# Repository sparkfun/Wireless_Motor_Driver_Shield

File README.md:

SparkFun Wireless Motor Driver Shield
=====================================

[*SparkFun Wireless Motor Driver Shield (DEV-14285)*](https://www.sparkfun.com/products/14285)
Arduino shield with built-in motor driver and XBee slot.

This is an Arduino shield that integrates an H-Bridge Driver and breaks out 
all I/O ports to three-pin headers on a GND / PWR / SIG standard. This enables quick
prototyping and integration of Arduino projects without the need of a breadboard.

This board contains an XBee header for adding wireless capability to your Arduino projects. A switch for 
SW_Serial ties the TX/RX lines to pins A0 and A1 on the Arduino board. 

This shield is a perfect addition to building up a simiple robotics platform with an
Arduino board. Two switches allow you to select which power source is used to power the motors and/or servos.
See [the hookup guide](https://learn.sparkfun.com/tutorials/wireless-motor-driver-shield-hookup-guide#hardware-overview) for a chart showing the various switch configurations.

**Note:** If connected to your Arduino, the switch must be set to SW_Serial in order to program your board. 

Repository Contents
-------------------

* **/Firmware** - Example code 
* **/Hardware** - Eagle design files (.brd, .sch)
* **/Production** - Production panel files (.brd)

Documentation
--------------
* **[Hookup Guide](https://learn.sparkfun.com/tutorials/wireless-motor-driver-shield-hookup-guide)** - Basic hookup guide for the Wireless Motor Driver Shield.
* **[SparkFun Fritzing repo](https://github.com/sparkfun/Fritzing_Parts)** - Fritzing diagrams for SparkFun products.
* **[SparkFun 3D Model repo](https://github.com/sparkfun/3D_Models)** - 3D models of SparkFun products. 

Version History
---------------
* [vH14](https://github.com/sparkfun/Ludus_ProtoShield_Wireless/tree/vH14) - Current version
* [vH11](https://github.com/sparkfun/Ludus_ProtoShield_Wireless/tree/V_1.1) - The product formerly known as the Ludus ProtoShield Wireless

License Information
-------------------

This product is _**open source**_! 

Please review the LICENSE.md file for license information. 

If you have any questions or concerns on licensing, please contact techsupport@sparkfun.com.

Distributed as-is; no warranty is given.

- Your friends at SparkFun.

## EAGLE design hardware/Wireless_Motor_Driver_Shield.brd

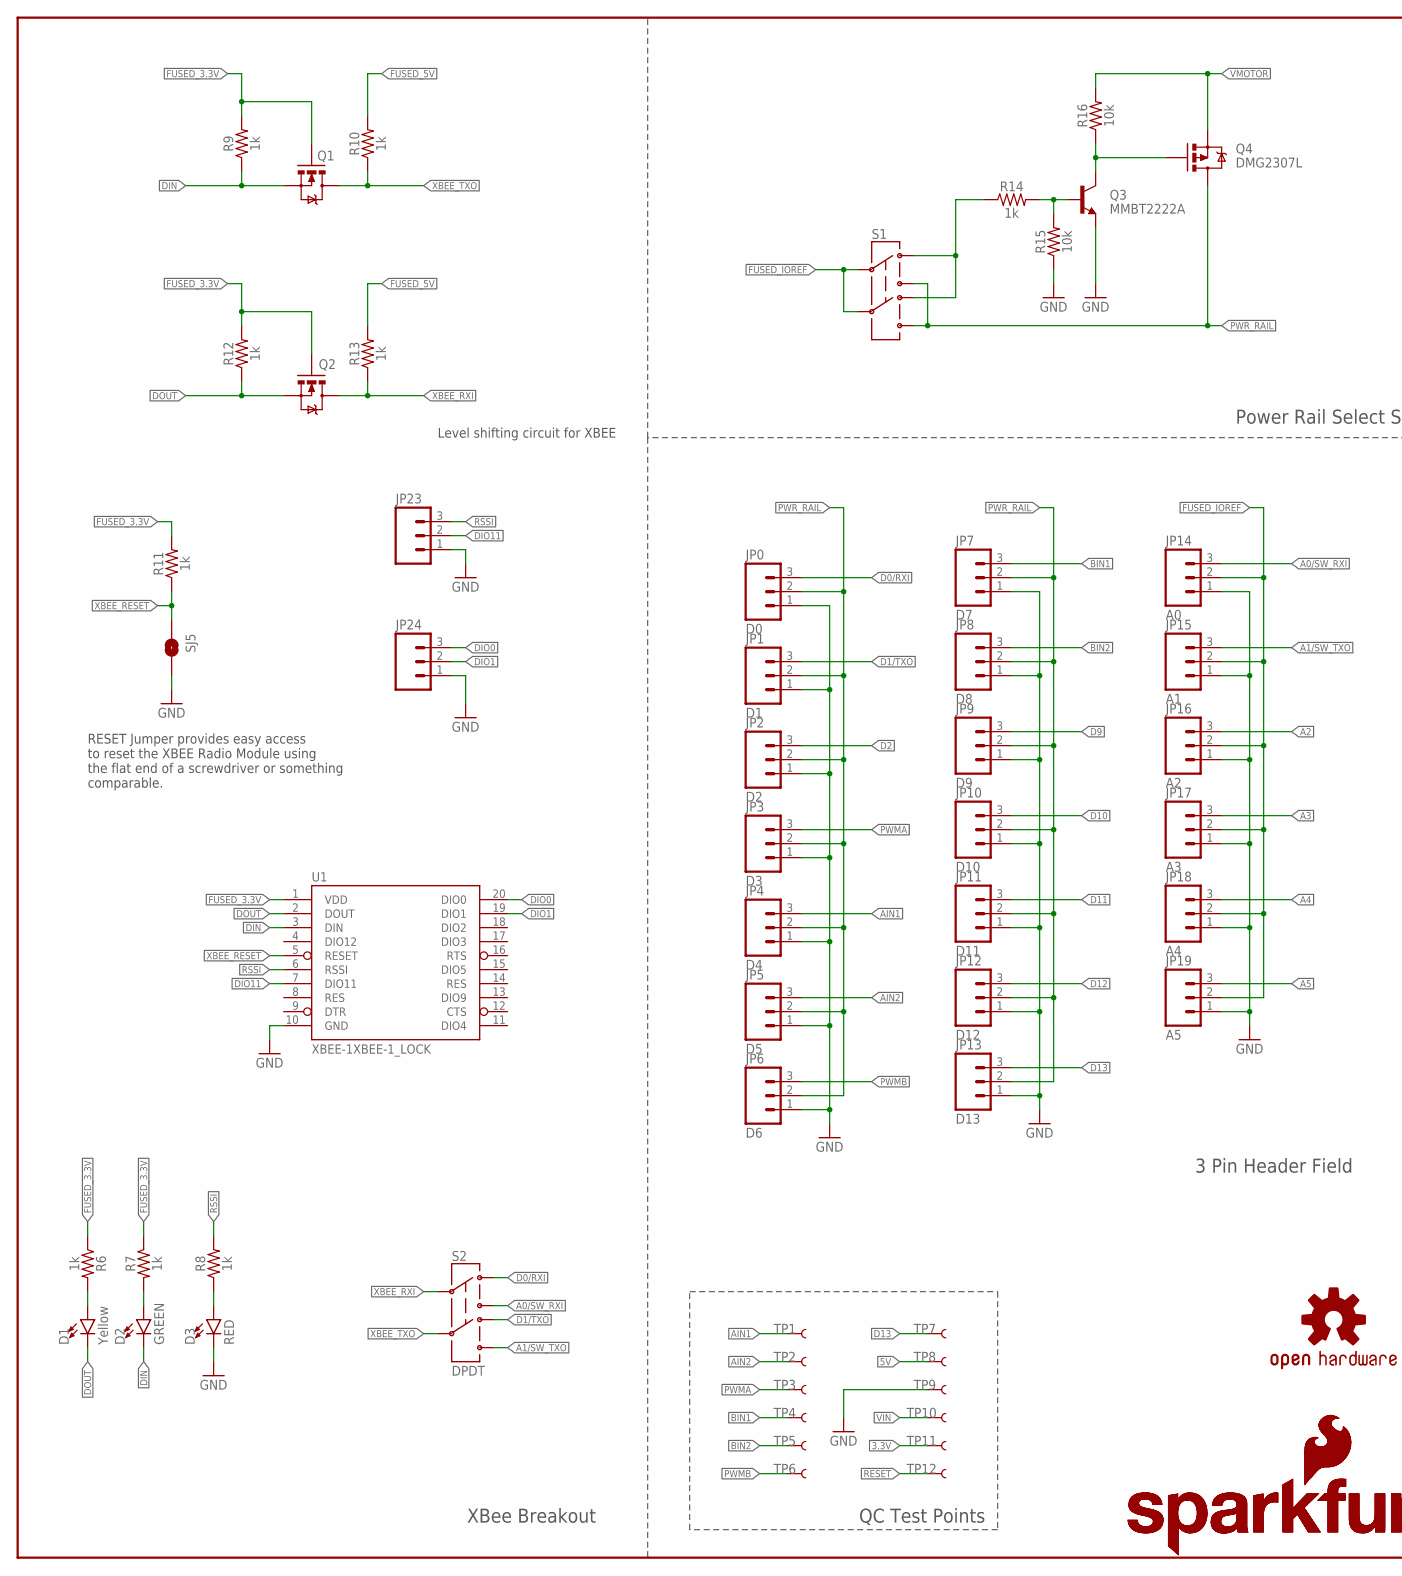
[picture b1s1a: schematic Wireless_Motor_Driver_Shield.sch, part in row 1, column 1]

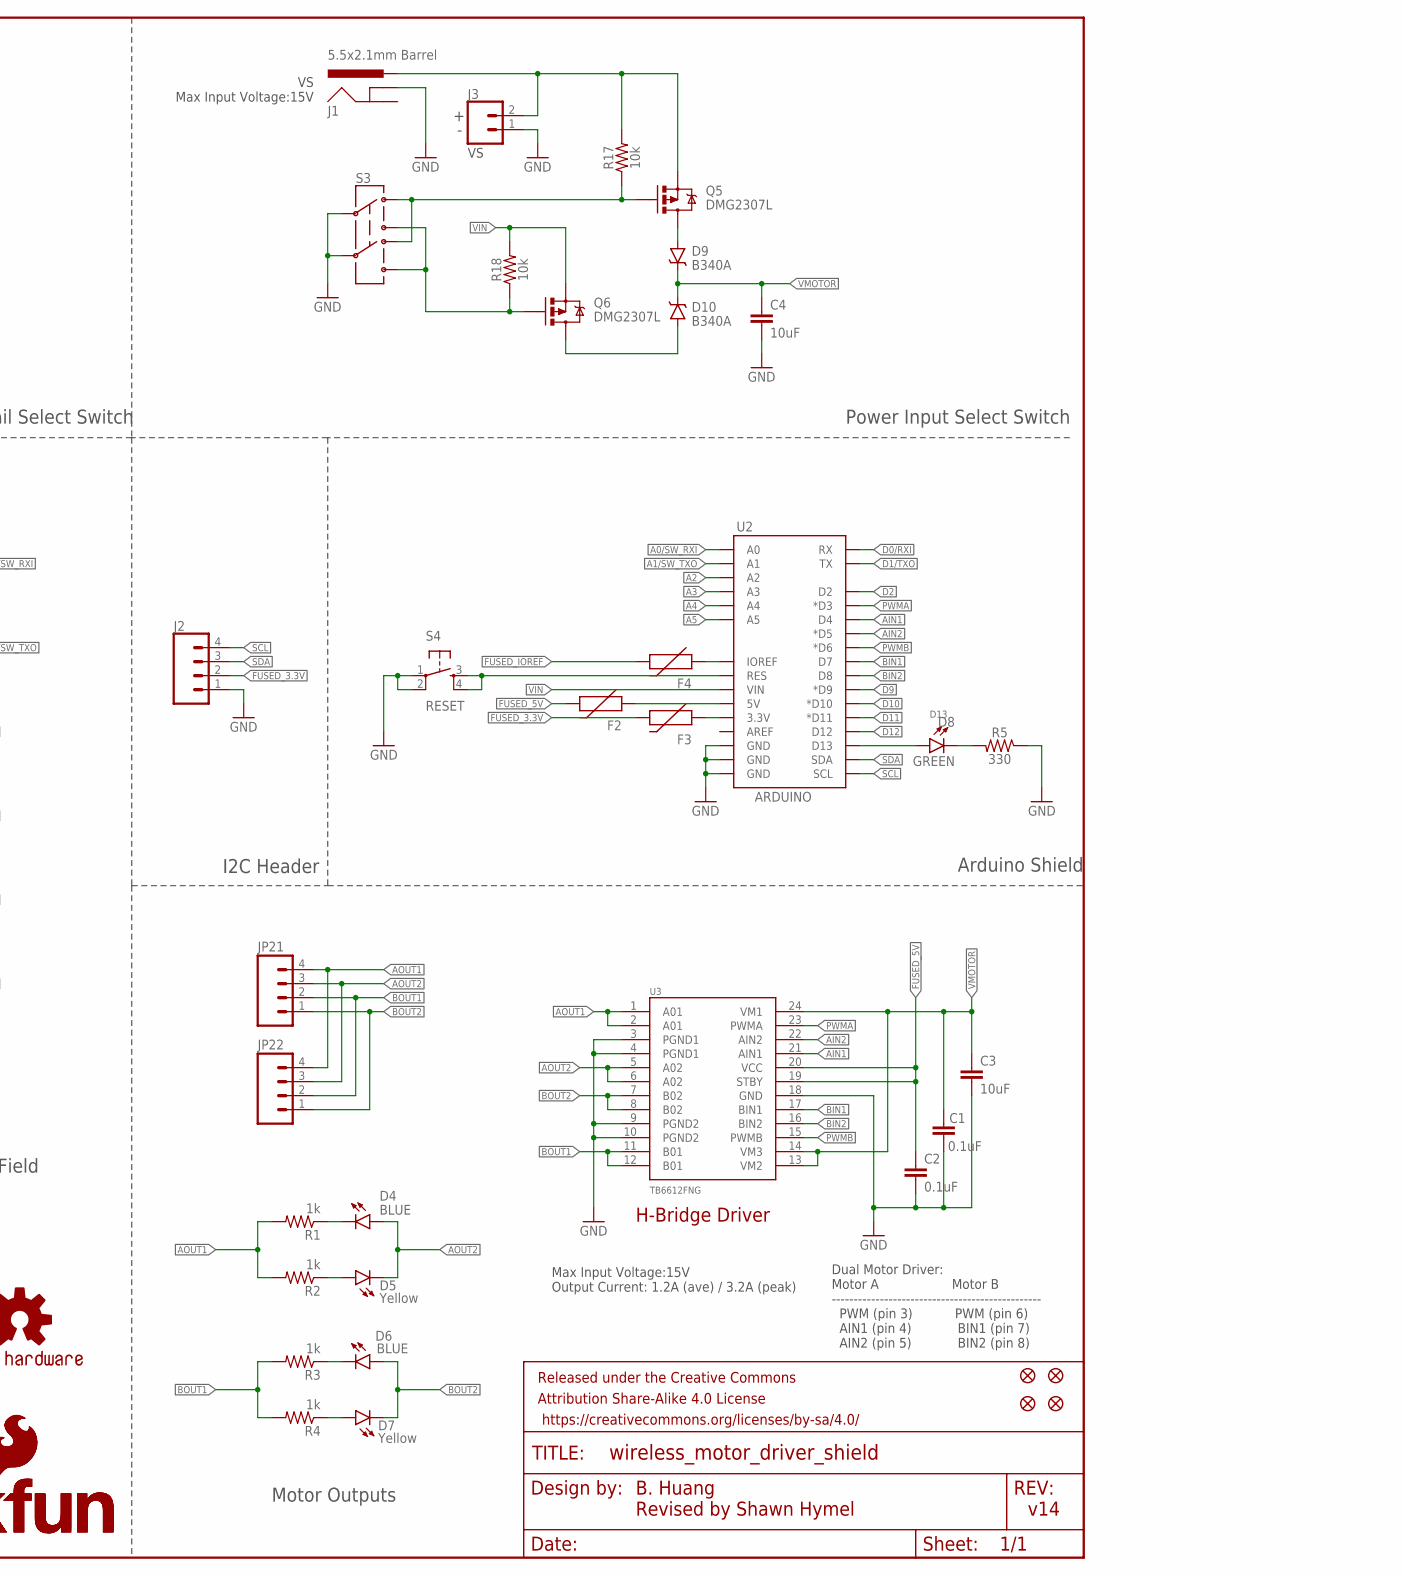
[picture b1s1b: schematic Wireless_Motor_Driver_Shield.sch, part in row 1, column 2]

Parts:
C1, C2: 0.1uF; 0603
C3, C4: 10uF; 1210
D1, D5, D7: Yellow; LED-0603
D2, D8: GREEN; LED-0603
D3: RED; LED-0603
D4, D6: BLUE; LED-0603
D9, D10: B340A; SMA-DIODE
F2, F3, F4: PTCSMD; PTC-1206
FID1, FID2, FID3, FID4: FIDUCIAL1X2; FIDUCIAL-1X2
FRAME1: FRAME-LEDGER; CREATIVE_COMMONS
J1: 5.5x2.1mm Barrel; POWER_JACK_SMD
J2: CONN_04SMD_RA_FEMALE; 1X04_SMD_RA_FEMALE
J3: CONN_021X02_NO_SILK; 1X02_NO_SILK
JP0: D0; 1X03_LOCK
JP1: D1; 1X03_LOCK
JP2: D2; 1X03_LOCK
JP3: D3; 1X03_LOCK
JP4: D4; 1X03_LOCK
JP5: D5; 1X03_LOCK
JP6: D6; 1X03_LOCK
JP7: D7; 1X03_LOCK
JP8: D8; 1X03_LOCK
JP9: D9; 1X03_LOCK
JP10: D10; 1X03_LOCK
JP11: D11; 1X03_LOCK
JP12: D12; 1X03_LOCK
JP13: D13; 1X03_LOCK
JP14: A0; 1X03_LOCK
JP15: A1; 1X03_LOCK
JP16: A2; 1X03_LOCK
JP17: A3; 1X03_LOCK
JP18: A4; 1X03_LOCK
JP19: A5; 1X03_LOCK
JP21: M04PTH; 1X04@1
JP22: M04LOCK; 1X04_LOCK@1
JP23, JP24: M031X03_NO_SILK; 1X03_NO_SILK
LOGO1: OSHW-LOGOM; OSHW-LOGO-M
LOGO2, LOGO4: SFE_LOGO_NAME_FLAME.1_INCH; SFE_LOGO_NAME_FLAME_.1
LOGO3: SFE_LOGO_FLAME.2_INCH; SFE_LOGO_FLAME_.2
Q1, Q2: MOSFET-NCHANNELBSS138; SOT23-3
Q3: MMBT2222A; SOT23-3
Q4, Q5, Q6: DMG2307L; SOT23-3
R1, R2, R3, R4, R6, R7, R8, R9, R10, R11, R12, R13, R14: 1k; 0603
R5: 330; 0603
R15, R16, R17, R18: 10k; 0603
S1, S3: SWITCH-DPDTAYZ0202; AYZ0202
S2: DPDT; AYZ0202
S4: RESET; TACTILE-SWITCH-SMD
SJ5: SOLDERJUMPERNO; SJ_2S-NO
TP1, TP2, TP3, TP4, TP5, TP6, TP7, TP8, TP9, TP10, TP11, TP12: TEST-POINT3X5; PAD.03X.05
U1: XBEE-1XBEE-1_LOCK; XBEE-1_LOCK
U2: ARDUINO; UNO_R3_SHIELD_NOLABELS_LOCK
U3: TB6612FNG; SSOP24

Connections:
3.3V: F3.1, TP11.P$1, U2.3.3V
5V: F2.1, TP8.P$1, U2.5V
A0/SW_RXI: JP14.3, S2.3, U2.A0
A1/SW_TXO: JP15.3, S2.6, U2.A1
A2: JP16.3, U2.A2
A3: JP17.3, U2.A3
A4: JP18.3, U2.A4
A5: JP19.3, U2.A5
AIN1: JP4.3, TP1.P$1, U2.D4, U3.21 (AIN1)
AIN2: JP5.3, TP2.P$1, U2.D5 (*D5), U3.22 (AIN2)
AOUT1: JP21.4, JP22.4, R1.2, R2.2, U3.1 (A01), U3.2 (A01)
AOUT2: D4.A, D5.C, JP21.3, JP22.3, U3.5 (A02), U3.6 (A02)
BIN1: JP7.3, TP4.P$1, U2.D7, U3.17 (BIN1)
BIN2: JP8.3, TP5.P$1, U2.D8, U3.16 (BIN2)
BOUT1: JP21.2, JP22.2, R3.2, R4.2, U3.11 (B01), U3.12 (B01)
BOUT2: D6.A, D7.C, JP21.1, JP22.1, U3.7 (B02), U3.8 (B02)
D0/RXI: JP0.3, S2.1, U2.RX
D1/TXO: JP1.3, S2.4, U2.TX
D2: JP2.3, U2.D2
D9: JP9.3, U2.D9 (*D9)
D10: JP10.3, U2.D10 (*D10)
D11: JP11.3, U2.D11 (*D11)
D12: JP12.3, U2.D12
D13: D8.A, JP13.3, TP7.P$1, U2.D13
DIN: D2.C, Q1.2 (S), R9.1, U1.3 (DIN)
DIO0: JP24.3, U1.20 (DIO0)
DIO1: JP24.2, U1.19 (DIO1)
DIO11: JP23.2, U1.7 (DIO11)
DOUT: D1.C, Q2.2 (S), R12.1, U1.2 (DOUT)
FUSED_3.3V: F3.2, J2.2, Q1.1 (G), Q2.1 (G), R6.1, R7.1, R9.2, R11.2, R12.2, U1.1 (VDD)
FUSED_5V: C2.1, F2.2, R10.2, R13.2, U3.19 (STBY), U3.20 (VCC)
FUSED_IOREF: F4.2, JP14.2, JP15.2, JP16.2, JP17.2, JP18.2, JP19.2, S1.2, S1.5
GND: C1.2, C2.2, C3.2, C4.2, D3.C, J1.GND (GNDBREAK), J2.1, J3.1, JP0.1, JP1.1, JP2.1, JP3.1, JP4.1, JP5.1, JP6.1, JP7.1, JP8.1, JP9.1, JP10.1, JP11.1, JP12.1, JP13.1, JP14.1, JP15.1, JP16.1, JP17.1, JP18.1, JP19.1, JP23.1, JP24.1, Q3.2 (E), R5.1, R15.1, S3.2, S3.5, S4.1, S4.2, SJ5.2, TP9.P$1, U1.10 (GND), U2.GND@0 (GND), U2.GND@1 (GND), U2.GND@2 (GND), U3.3 (PGND1), U3.4 (PGND1), U3.9 (PGND2), U3.10 (PGND2), U3.18 (GND)
IOREF: F4.1, U2.IOREF
unnamed: D8.C, R5.2
unnamed: Q3.1 (B), R14.2, R15.2
unnamed: D5.A, R2.1
unnamed: Q6.1 (G), R18.1, S3.3, S3.6
unnamed: D4.C, R1.1
unnamed: D7.A, R4.1
unnamed: D6.C, R3.1
unnamed: J1.VIN0 (PWR), J3.2, Q5.2 (S), R17.2
unnamed: Q3.3 (C), Q4.1 (G), R16.1
unnamed: Q5.1 (G), R17.1, S3.1, S3.4
unnamed: R14.1, S1.1, S1.4
unnamed: D9.A, Q5.3 (D)
unnamed: D10.A, Q6.3 (D)
unnamed: D1.A, R6.2
unnamed: D2.A, R7.2
unnamed: D3.A, R8.1
PWMA: JP3.3, TP3.P$1, U2.D3 (*D3), U3.23 (PWMA)
PWMB: JP6.3, TP6.P$1, U2.D6 (*D6), U3.15 (PWMB)
PWR_RAIL: JP0.2, JP1.2, JP2.2, JP3.2, JP4.2, JP5.2, JP6.2, JP7.2, JP8.2, JP9.2, JP10.2, JP11.2, JP12.2, JP13.2, Q4.3 (D), S1.3, S1.6
RESET: S4.3, S4.4, TP12.P$1, U2.RES
RSSI: JP23.3, R8.2, U1.6 (RSSI)
SCL: J2.4, U2.SCL
SDA: J2.3, U2.SDA
VIN: Q6.2 (S), R18.2, TP10.P$1, U2.VIN
VMOTOR: C1.1, C3.1, C4.1, D9.C, D10.C, Q4.2 (S), R16.2, U3.13 (VM2), U3.14 (VM3), U3.24 (VM1)
XBEE_RESET: R11.1, SJ5.1, U1.5 (RESET)
XBEE_RXI: Q2.3 (D), R13.1, S2.2
XBEE_TXO: Q1.3 (D), R10.1, S2.5

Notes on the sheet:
Arduino Shield
H-Bridge Driver
Motor Outputs
B. Huang Revised by Shawn Hymel
v14
I2C Header
3 Pin Header Field
XBee Breakout
Power Rail Select Switch
Max Input Voltage:15V Output Current: 1.2A (ave) / 3.2A (peak)
RESET Jumper provides easy access to reset the XBEE Radio Module using the flat end of a screwdriver or something comparable.
Level shifting circuit for XBEE
QC Test Points
Dual Motor Driver: Motor A Motor B ------------------------------------------------ PWM (pin 3) PWM (pin 6) AIN1 (pin 4) BIN1 (pin 7) AIN2 (pin 5) BIN2 (pin 8)
Power Input Select Switch
VS Max Input Voltage:15V

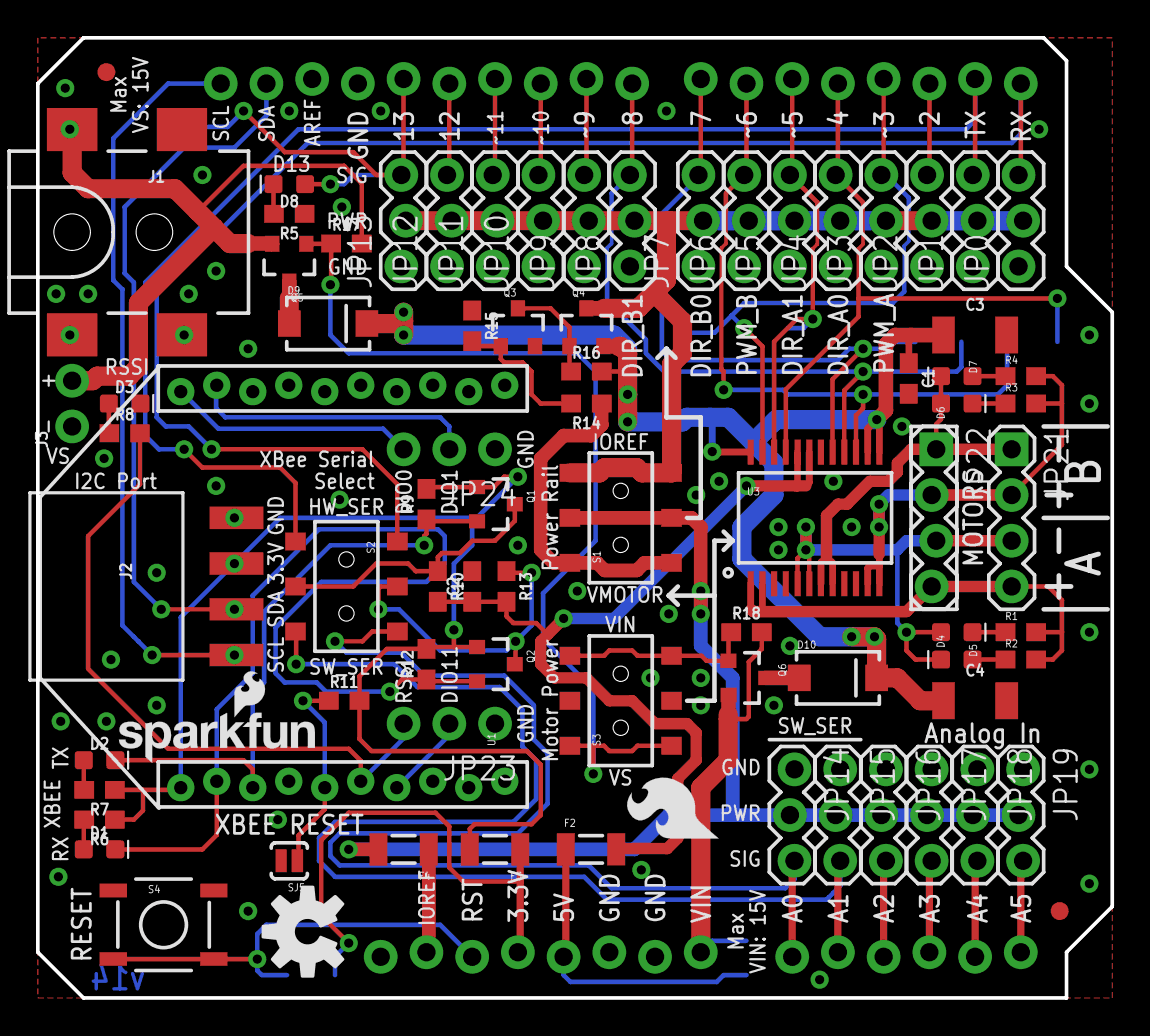
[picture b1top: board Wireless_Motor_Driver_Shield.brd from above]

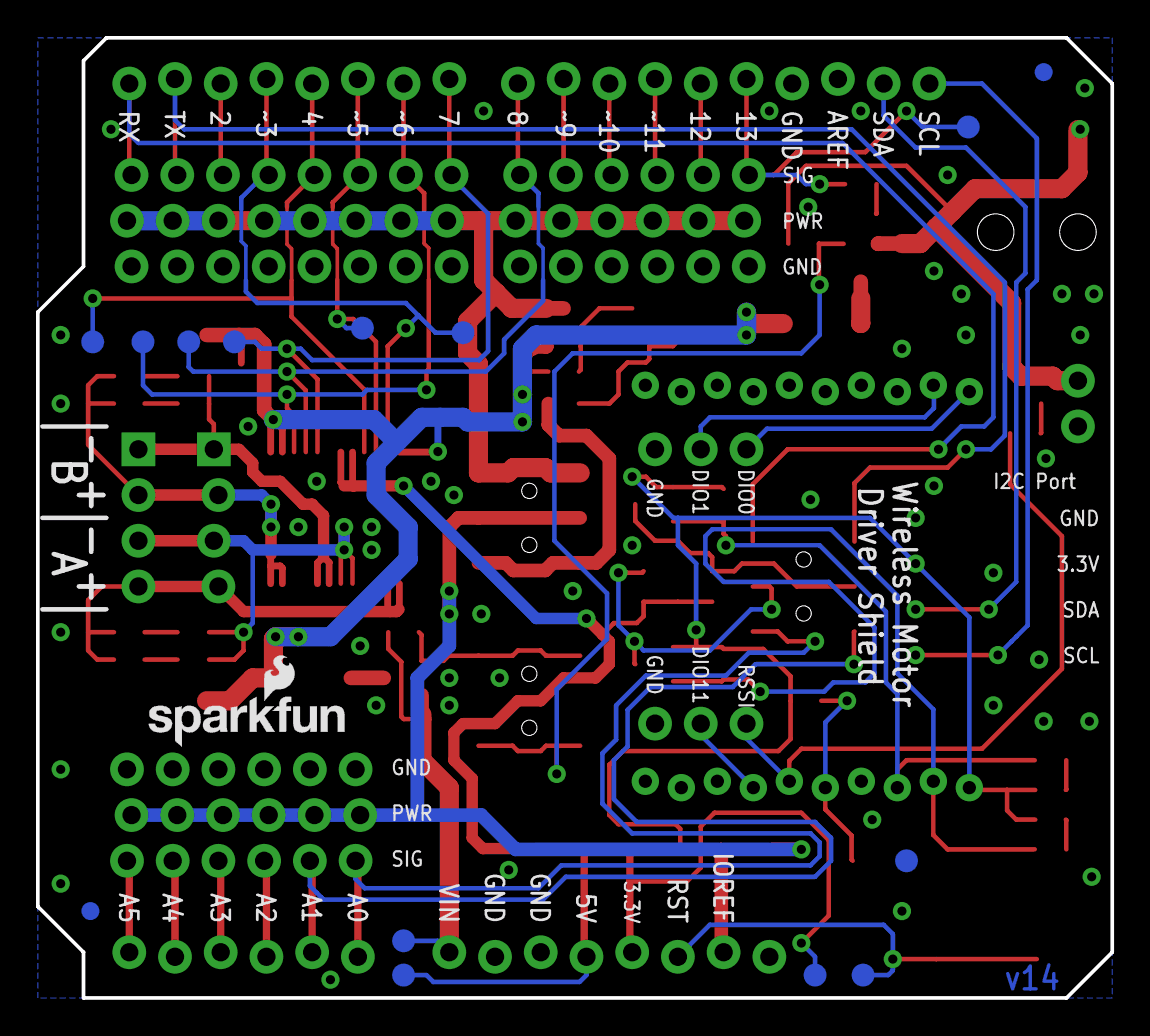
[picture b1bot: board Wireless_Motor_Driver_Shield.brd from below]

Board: 2 copper layers, 59.7 x 53.3 mm, 97 parts (15 on the bottom side), 62 nets.

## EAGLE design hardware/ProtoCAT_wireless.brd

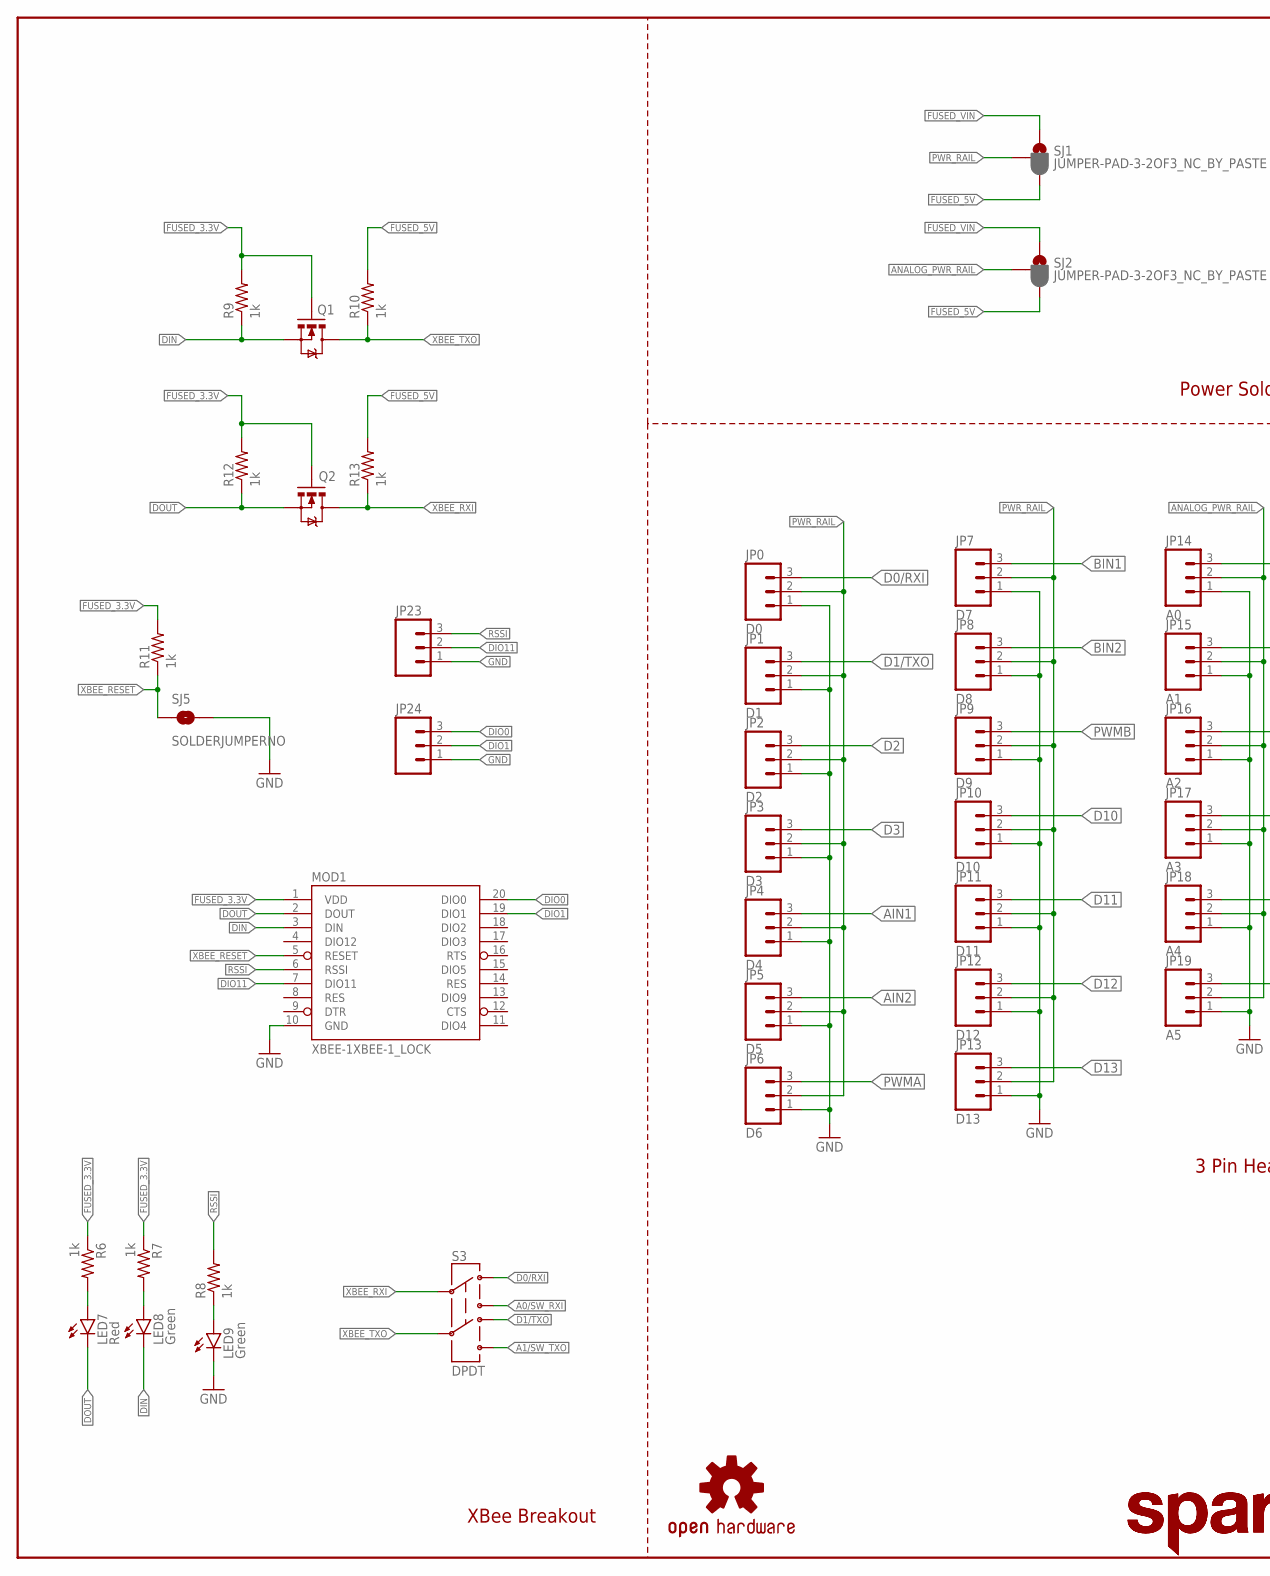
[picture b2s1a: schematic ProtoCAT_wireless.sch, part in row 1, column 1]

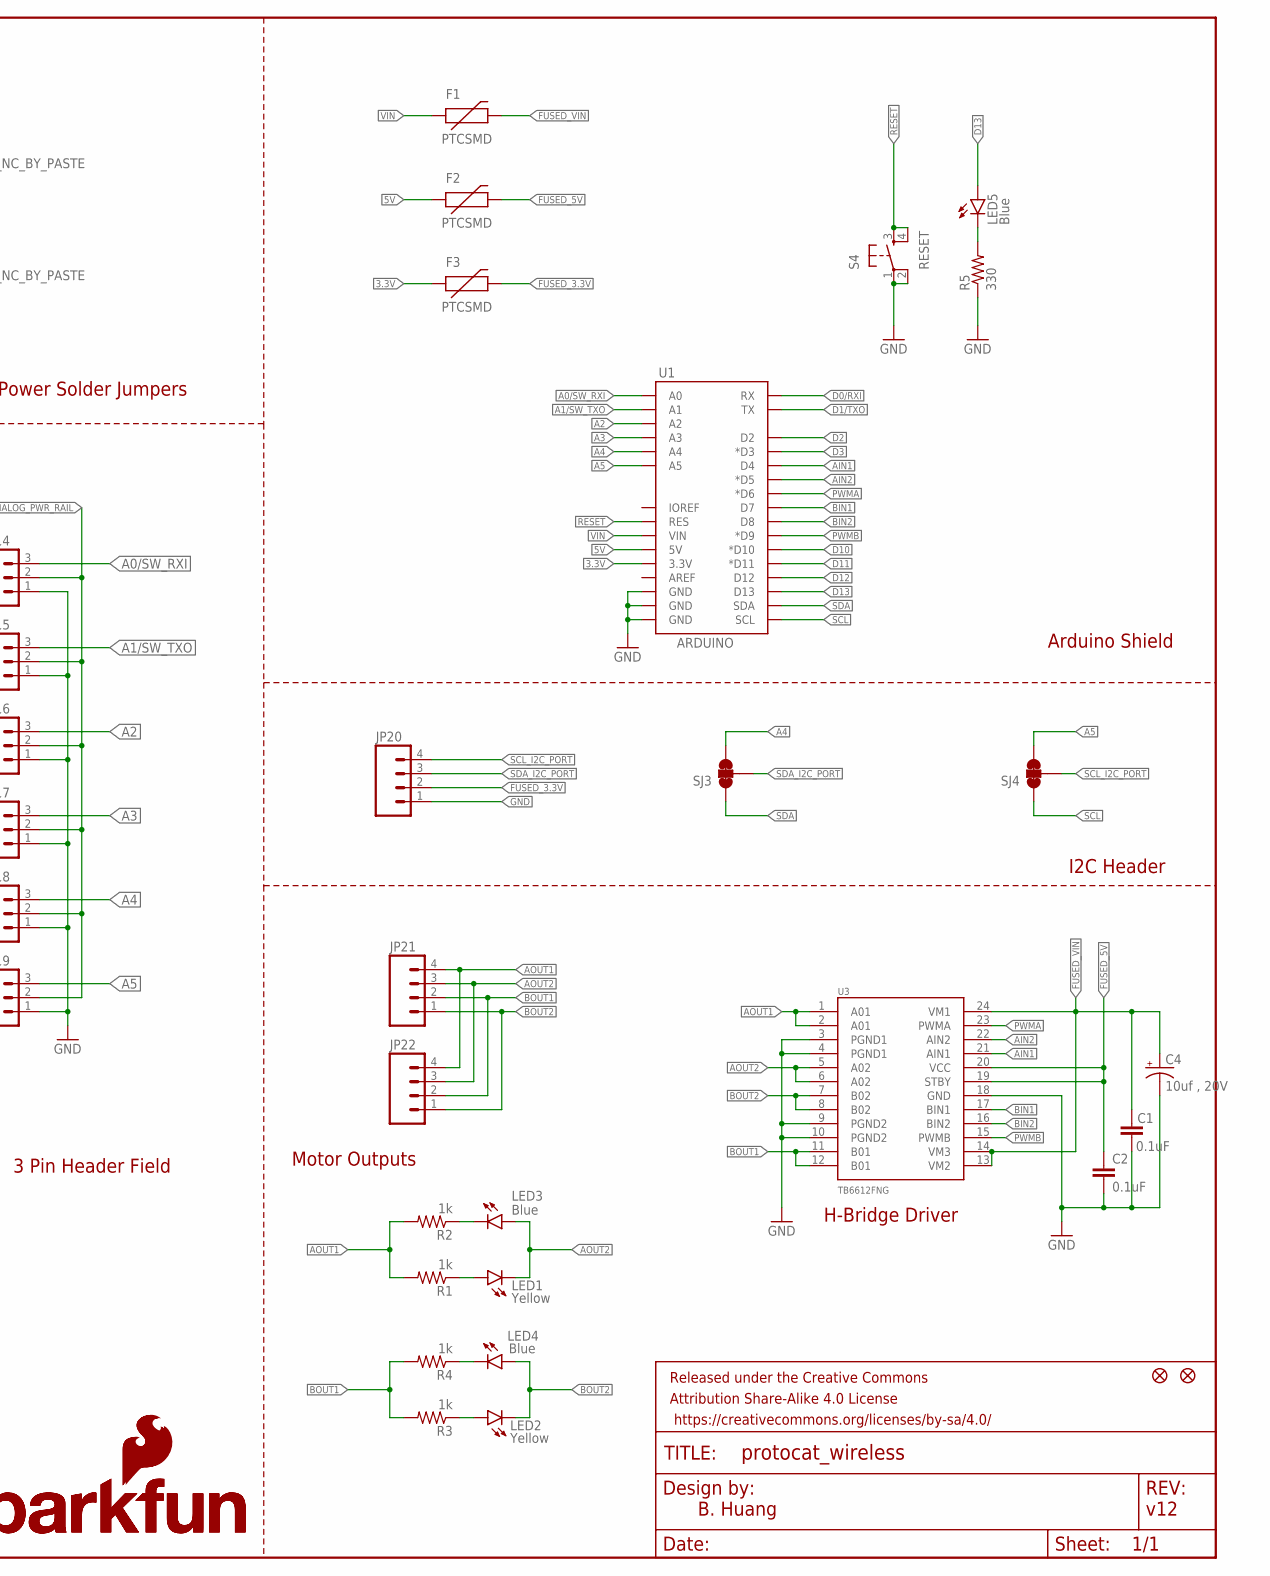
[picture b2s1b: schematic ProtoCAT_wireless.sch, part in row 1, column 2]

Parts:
C1, C2: 0.1uF; 0603-CAP
C4: 10uf , 20V; EIA3528
F1, F2, F3: PTCSMD; PTC-1206
FID1, FID2: FIDUCIAL1X2; FIDUCIAL-1X2
FRAME1: FRAME-LEDGER; CREATIVE_COMMONS
JP0: D0; 1X03_LOCK
JP1: D1; 1X03_LOCK
JP2: D2; 1X03_LOCK
JP3: D3; 1X03_LOCK
JP4: D4; 1X03_LOCK
JP5: D5; 1X03_LOCK
JP6: D6; 1X03_LOCK
JP7: D7; 1X03_LOCK
JP8: D8; 1X03_LOCK
JP9: D9; 1X03_LOCK
JP10: D10; 1X03_LOCK
JP11: D11; 1X03_LOCK
JP12: D12; 1X03_LOCK
JP13: D13; 1X03_LOCK
JP14: A0; 1X03_LOCK
JP15: A1; 1X03_LOCK
JP16: A2; 1X03_LOCK
JP17: A3; 1X03_LOCK
JP18: A4; 1X03_LOCK
JP19: A5; 1X03_LOCK
JP20, JP21: M04PTH; 1X04
JP22: M04SMD_STRAIGHT_COMBO; 1X04_SMD_STRAIGHT_COMBO
JP23, JP24: M031X03_NO_SILK; 1X03_NO_SILK
LED1, LED2: Yellow; LED-0603
LED3, LED4, LED5: Blue; LED-0603
LED7: Red; LED-0603
LED8, LED9: Green; LED-0603
LOGO1: OSHW-LOGOM; OSHW-LOGO-M
LOGO2, LOGO4: SFE_LOGO_NAME_FLAME.1_INCH; SFE_LOGO_NAME_FLAME_.1
LOGO3: SFE_LOGO_FLAME.2COP; SFE_LOGO_FLAME_COPPER_.2
MOD1: XBEE-1XBEE-1_LOCK; XBEE-1_LOCK
Q1, Q2: MOSFET-NCHANNELSMD; SOT23-3
R1, R2, R3, R4, R6, R7, R8, R9, R10, R11, R12, R13: 1k; 0603-RES
R5: 330; 0603-RES
S3: DPDT; AYZ0202
S4: RESET; TACTILE-SWITCH-SMD
SJ1, SJ2: JUMPER-PAD-3-2OF3_NC_BY_PASTE; PAD-JUMPER-3-2OF3_NC_BY_PASTE_YES_SILK_FULL_BOX
SJ3, SJ4: JUMPER-PAD-3-NC_BY_TRACE; PAD-JUMPER-3-3OF3_NC_BY_TRACE_YES_SILK_FULL_BOX
SJ5: SOLDERJUMPERNO; SJ_2S-NO
U1: ARDUINO; UNO_R3_SHIELD_NOLABELS
U3: TB6612FNG; SSOP24
U$1: SFE_LUDUS; SFE_LUDUS-M

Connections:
3.3V: F3.1, U1.3.3V
5V: F2.1, U1.5V
A0/SW_RXI: JP14.3, S3.3, U1.A0
A1/SW_TXO: JP15.3, S3.6, U1.A1
A2: JP16.3, U1.A2
A3: JP17.3, U1.A3
A4: JP18.3, SJ3.3, U1.A4
A5: JP19.3, SJ4.3, U1.A5
AIN1: JP4.3, U1.D4, U3.21 (AIN1)
AIN2: JP5.3, U1.D5 (*D5), U3.22 (AIN2)
ANALOG_PWR_RAIL: JP14.2, JP15.2, JP16.2, JP17.2, JP18.2, JP19.2, SJ2.2
AOUT1: JP21.4, JP22.4, R1.2, R2.2, U3.1 (A01), U3.2 (A01)
AOUT2: JP21.3, JP22.3, LED1.C, LED3.A, U3.5 (A02), U3.6 (A02)
BIN1: JP7.3, U1.D7, U3.17 (BIN1)
BIN2: JP8.3, U1.D8, U3.16 (BIN2)
BOUT1: JP21.2, JP22.2, R3.2, R4.2, U3.11 (B01), U3.12 (B01)
BOUT2: JP21.1, JP22.1, LED2.C, LED4.A, U3.7 (B02), U3.8 (B02)
D0/RXI: JP0.3, S3.1, U1.RX
D1/TXO: JP1.3, S3.4, U1.TX
D2: JP2.3, U1.D2
D3: JP3.3, U1.D3 (*D3)
D10: JP10.3, U1.D10 (*D10)
D11: JP11.3, U1.D11 (*D11)
D12: JP12.3, U1.D12
D13: JP13.3, LED5.A, U1.D13
DIN: LED8.C, MOD1.3 (DIN), Q1.2 (S), R9.1
DIO0: JP24.3, MOD1.20 (DIO0)
DIO1: JP24.2, MOD1.19 (DIO1)
DIO11: JP23.2, MOD1.7 (DIO11)
DOUT: LED7.C, MOD1.2 (DOUT), Q2.2 (S), R12.1
FUSED_3.3V: F3.2, JP20.2, MOD1.1 (VDD), Q1.1 (G), Q2.1 (G), R6.1, R7.1, R9.2, R11.2, R12.2
FUSED_5V: C2.1, F2.2, R10.2, R13.2, SJ1.3, SJ2.3, U3.19 (STBY), U3.20 (VCC)
FUSED_VIN: C1.1, C4.A (+), F1.2, SJ1.1, SJ2.1, U3.13 (VM2), U3.14 (VM3), U3.24 (VM1)
GND: C1.2, C2.2, C4.C (-), JP0.1, JP1.1, JP2.1, JP3.1, JP4.1, JP5.1, JP6.1, JP7.1, JP8.1, JP9.1, JP10.1, JP11.1, JP12.1, JP13.1, JP14.1, JP15.1, JP16.1, JP17.1, JP18.1, JP19.1, JP20.1, JP23.1, JP24.1, LED9.C, MOD1.10 (GND), R5.1, S4.1, S4.2, SJ5.2, U1.GND@0 (GND), U1.GND@1 (GND), U1.GND@2 (GND), U3.3 (PGND1), U3.4 (PGND1), U3.9 (PGND2), U3.10 (PGND2), U3.18 (GND)
unnamed: LED5.C, R5.2
unnamed: LED1.A, R1.1
unnamed: LED3.C, R2.1
unnamed: LED2.A, R3.1
unnamed: LED4.C, R4.1
unnamed: LED7.A, R6.2
unnamed: LED8.A, R7.2
unnamed: LED9.A, R8.1
PWMA: JP6.3, U1.D6 (*D6), U3.23 (PWMA)
PWMB: JP9.3, U1.D9 (*D9), U3.15 (PWMB)
PWR_RAIL: JP0.2, JP1.2, JP2.2, JP3.2, JP4.2, JP5.2, JP6.2, JP7.2, JP8.2, JP9.2, JP10.2, JP11.2, JP12.2, JP13.2, SJ1.2
RESET: S4.3, S4.4, U1.RES
RSSI: JP23.3, MOD1.6 (RSSI), R8.2
SCL: SJ4.1, U1.SCL
SCL_I2C_PORT: JP20.4, SJ4.2
SDA: SJ3.1, U1.SDA
SDA_I2C_PORT: JP20.3, SJ3.2
VIN: F1.1, U1.VIN
XBEE_RESET: MOD1.5 (RESET), R11.1, SJ5.1
XBEE_RXI: Q2.3 (D), R13.1, S3.2
XBEE_TXO: Q1.3 (D), R10.1, S3.5

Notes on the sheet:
Arduino Shield
H-Bridge Driver
Motor Outputs
B. Huang
v12
I2C Header
3 Pin Header Field
XBee Breakout
Power Solder Jumpers

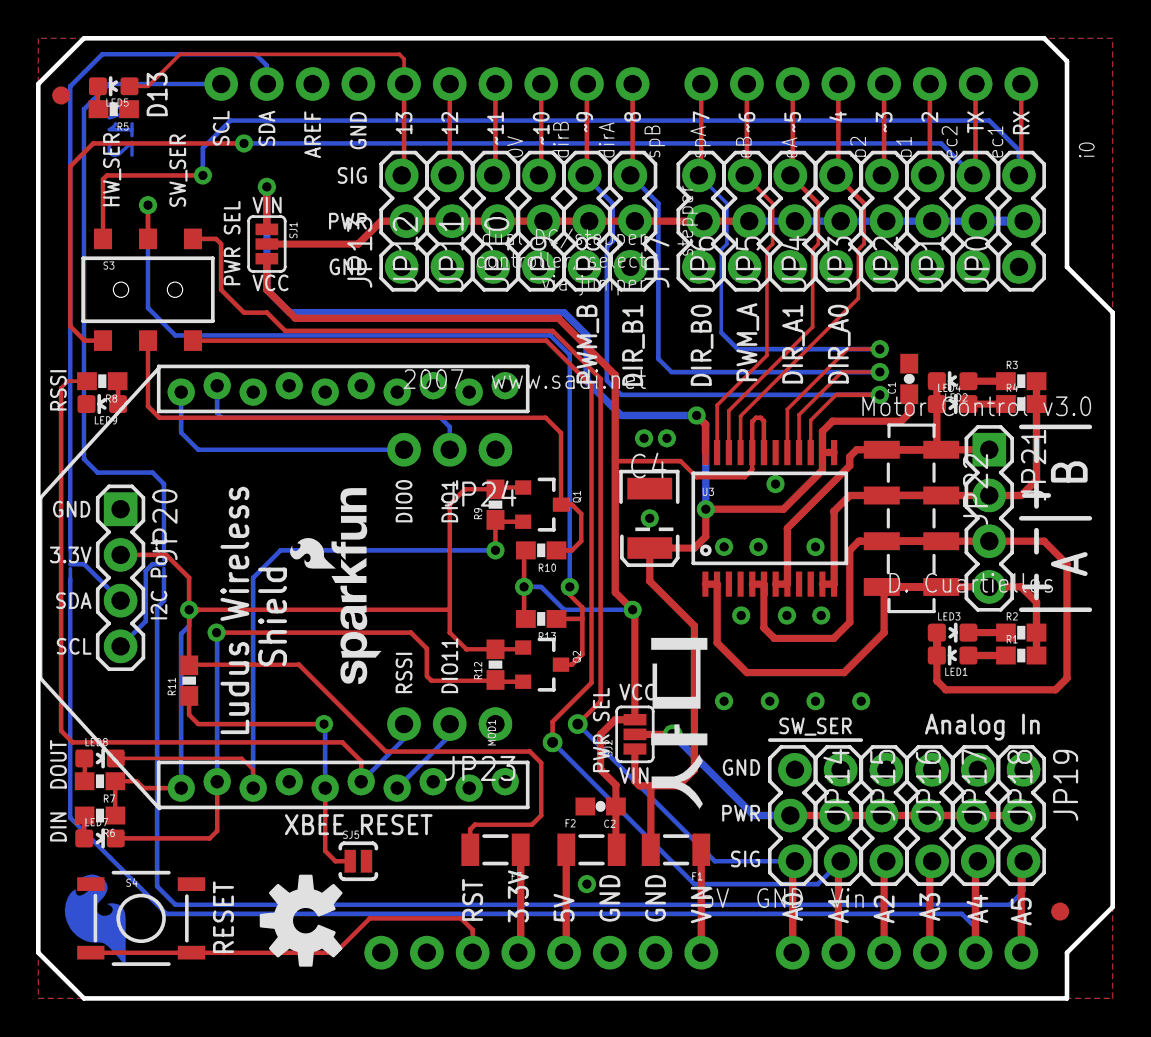
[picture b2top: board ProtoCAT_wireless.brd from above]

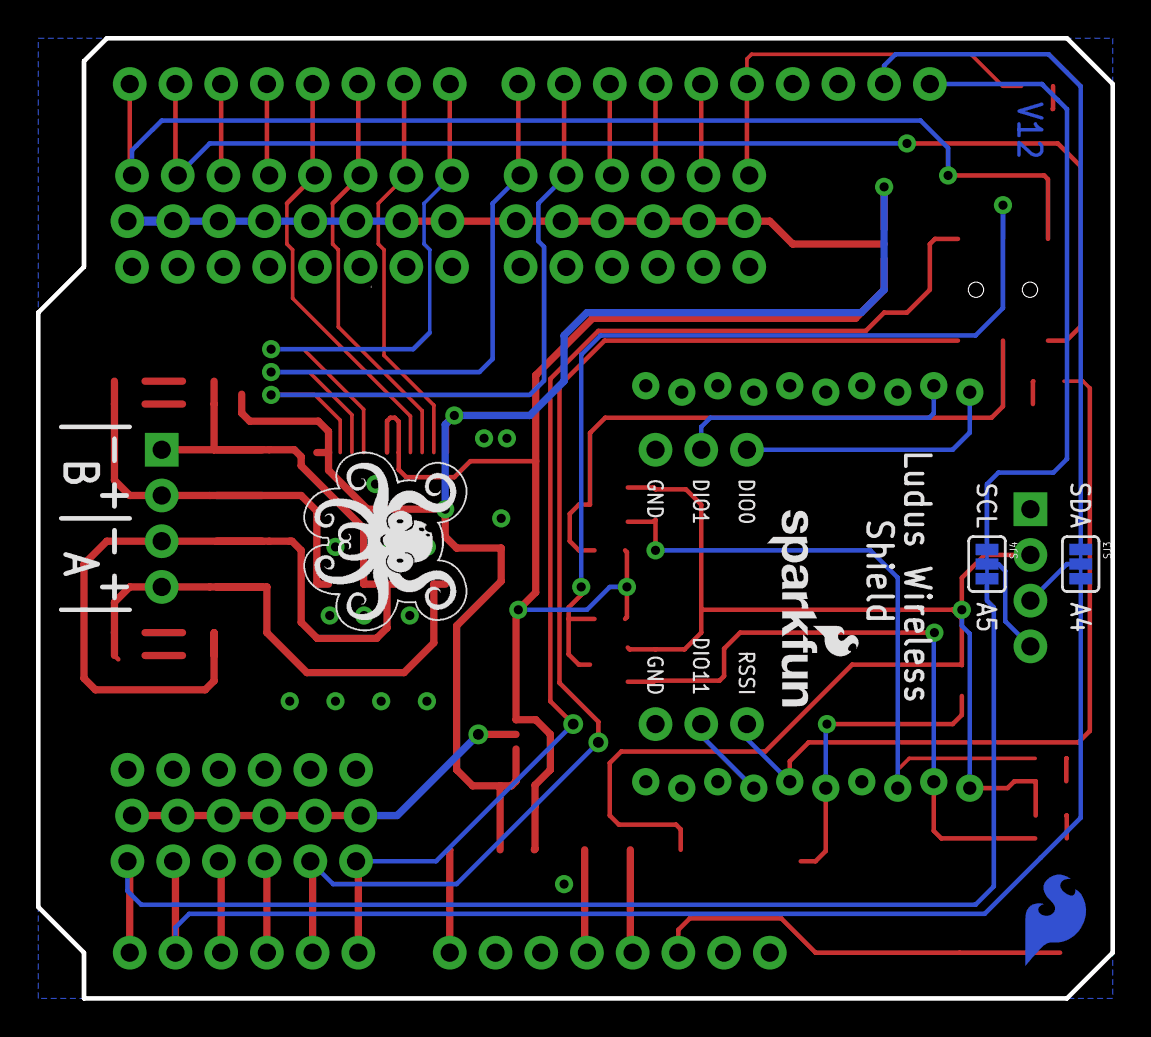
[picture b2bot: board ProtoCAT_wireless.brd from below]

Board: 2 copper layers, 59.7 x 53.3 mm, 72 parts (4 on the bottom side), 55 nets.

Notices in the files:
parts and their libraries:
SparkFun-Connectors: Licensing: CC v3.0 Share-Alike You are welcome to use this library for commercial purposes.
SparkFun-Boards: Licensing: Creative Commons ShareAlike 4.0 International - https://creativecommons.org/licenses/by-sa/4.0
SparkFun-Aesthetics: Released under the Creative Commons
